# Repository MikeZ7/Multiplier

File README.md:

# Multiplier

Project of four quadrant multiplier for Systems and Electronics Circuits subject

---

## Project description
* Power Supply: (4V - 6V) DC
* Input signals range: (-1.5V - 1.5V) DC/AC
* PCB dimensions: 60x30mm 
* PCB components size: 0805
  
---

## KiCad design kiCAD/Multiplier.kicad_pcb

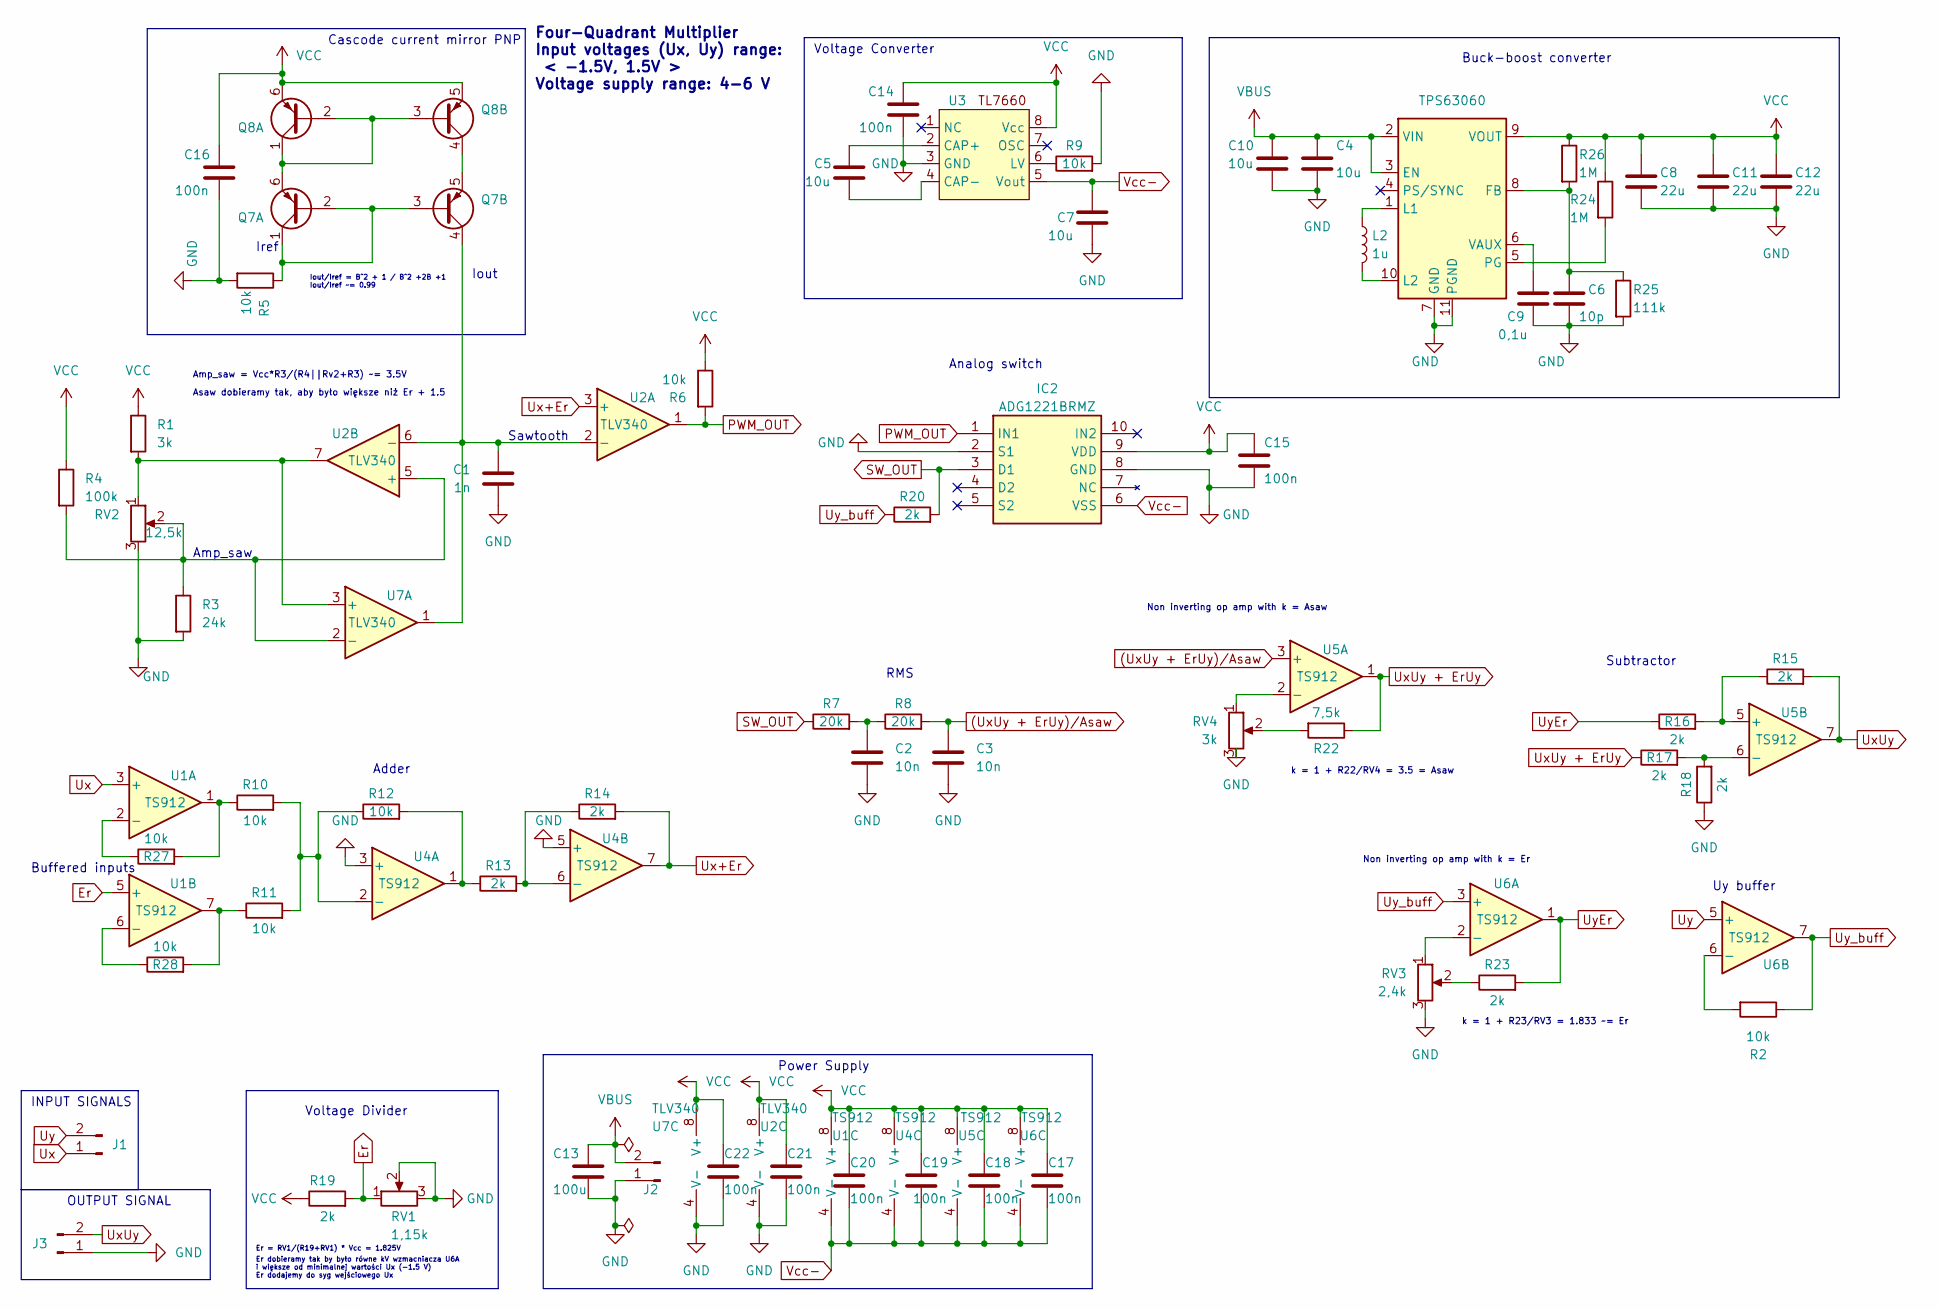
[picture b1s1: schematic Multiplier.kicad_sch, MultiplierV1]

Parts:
C1: 1n; C_0805_2012Metric
C2, C3: 10n; C_0805_2012Metric
C4, C5, C7, C10: 10u; C_0805_2012Metric
C6: 10p; C_0805_2012Metric
C8, C11, C12: 22u; C_0805_2012Metric
C9: 0,1u; C_0805_2012Metric
C13: 100u; CAP_293D-B_VSS
C14, C15, C16, C17, C18, C19, C20, C21, C22: 100n; C_0805_2012Metric
IC2: ADG1221BRMZ; RM_10_ADI; Mouser Part Number 584-ADG1221BRMZ
J1, J2, J3: Conn_01x02_Pin; PinHeader_1x02_P2.54mm_Vertical
L2: 1u; L_0805_2012Metric
Q7, Q8: Q_Dual_PNP_PNP_C1B1B2C2E2E1; SOT-363_DUAL_PNP
R1: 3k; R_0805_2012Metric_Pad1.20x1.40mm_HandSolder
R2, R5, R6, R9, R10, R11, R12, R27, R28: 10k; R_0805_2012Metric_Pad1.20x1.40mm_HandSolder
R3: 24k; R_0805_2012Metric_Pad1.20x1.40mm_HandSolder
R4: 100k; R_0805_2012Metric_Pad1.20x1.40mm_HandSolder
R7, R8: 20k; R_0805_2012Metric_Pad1.20x1.40mm_HandSolder
R13, R14, R15, R16, R17, R18, R19, R20, R23: 2k; R_0805_2012Metric_Pad1.20x1.40mm_HandSolder
R22: 7,5k; R_0805_2012Metric_Pad1.20x1.40mm_HandSolder
R24, R26: 1M; R_0805_2012Metric_Pad1.20x1.40mm_HandSolder
R25: 111k; R_0805_2012Metric_Pad1.20x1.40mm_HandSolder
RV1: 1,15k; Potentiometer_Bourns_3314G_Vertical
RV2: 12,5k; Potentiometer_Bourns_3314G_Vertical
RV3: 2,4k; Potentiometer_Bourns_3314G_Vertical
RV4: 3k; Potentiometer_Bourns_3314G_Vertical
U1, U4, U5, U6: TS912; TS912AIDT-SOIC8
U2, U7: TLV340; TLV3402IDR_SOIC8
U3: D8
U10: TPS63060; Texas_S-PWSON-N10_ThermalVias_Custom

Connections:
(UxUy + ErUy)/Asaw: C3.1, R8.2, U5.3 (+)
Er: R19.2, RV1.1, U1.5 (+)
GND: C1.2, C2.2, C3.2, C4.2, C6.2, C7.2, C8.2, C9.2, C10.2, C11.2, C12.2, C13.2, C14.2, C15.2, C16.2, C21.2, C22.2, IC2.2 (S1), IC2.8 (GND), J2.1, J3.1, R3.2, R5.2, R9.2, R18.1, R25.2, RV1.2, RV1.3, RV2.3, RV3.3, RV4.3, U2.4 (V-), U3.3 (GND), U4.3 (+), U4.5 (+), U7.4 (V-), U10.7 (GND), U10.11 (PGND); also elsewhere on the board
unnamed: C2.1, R7.2, R8.1
unnamed: Q7.1 (C1), Q7.2 (B1), Q7.3 (B2), R5.1
unnamed: Q7.6 (E1), Q8.1 (C1), Q8.2 (B1), Q8.3 (B2)
unnamed: C1.1, Q7.4 (C2), U2.2 (-), U2.6 (-), U7.1
unnamed: Q7.5 (E2), Q8.4 (C2)
unnamed: R10.1, R27.2, U1.1
unnamed: R11.1, R28.2, U1.7
unnamed: R12.2, R13.1, U4.1
unnamed: R22.2, RV4.2
unnamed: R23.1, RV3.2
unnamed: R27.1, U1.2 (-)
unnamed: R28.1, U1.6 (-)
unnamed: R3.1, R4.2, RV2.2, U2.5 (+), U7.2 (-)
unnamed: C5.1, U3.2 (CAP+)
unnamed: C5.2, U3.4 (CAP-)
unnamed: R9.1, U3.6 (LV)
unnamed: R10.2, R11.2, R12.1, U4.2 (-)
unnamed: R13.2, R14.1, U4.6 (-)
unnamed: RV4.1, U5.2 (-)
unnamed: R15.1, R16.2, U5.5 (+)
unnamed: R17.2, R18.2, U5.6 (-)
unnamed: RV3.1, U6.2 (-)
unnamed: R2.2, U6.6 (-)
unnamed: R1.2, RV2.1, U2.7, U7.3 (+)
unnamed: C6.1, R25.1, R26.2, U10.8 (FB)
unnamed: L2.1, U10.1 (L1)
unnamed: L2.2, U10.10 (L2)
unnamed: R24.2, U10.5 (PG)
unnamed: C9.1, U10.6 (VAUX)
PWM_OUT: IC2.1 (IN1), R6.2, U2.1
SW_OUT: IC2.3 (D1), R7.1, R20.2
Ux: J1.1, U1.3 (+); also elsewhere on the board
Ux+Er: R14.2, U2.3 (+), U4.7
UxUy: J3.2, R15.2, U5.7; also elsewhere on the board
UxUy + ErUy: R17.1, R22.1, U5.1
Uy: J1.2, U6.5 (+); also elsewhere on the board
UyEr: R16.1, R23.2, U6.1
Uy_buff: R2.1, R20.1, U6.3 (+), U6.7
VBUS: C4.1, C10.1, C13.1, J2.2, U10.2 (VIN), U10.3 (EN); also elsewhere on the board
VCC: C8.1, C11.1, C12.1, C14.1, C15.1, C16.1, C17.1, C18.1, C19.1, C20.1, C21.1, C22.1, IC2.9 (VDD), Q8.5 (E2), Q8.6 (E1), R1.1, R4.1, R6.1, R19.1, R24.1, R26.1, U1.8 (V+), U2.8 (V+), U3.8 (Vcc), U4.8 (V+), U5.8 (V+), U6.8 (V+), U7.8 (V+), U10.9 (VOUT)
Vcc-: C7.1, C17.2, C18.2, C19.2, C20.2, IC2.6 (VSS), U1.4 (V-), U3.5 (Vout), U4.4 (V-), U5.4 (V-), U6.4 (V-)

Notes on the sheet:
Non inverting op amp with k = Er
Cascode current mirror PNP
Iref
Analog switch
Iout
Iout/Iref = B^2 + 1 / B^2 +2B +1
OUTPUT SIGNAL
Non inverting op amp with k = Asaw
Buffered inputs
RMS
Amp_saw
Four-Quadrant Multiplier Input voltages (Ux, Uy) range: < -1.5V, 1.5V > Voltage supply range: 4-6 V
Er dobieramy tak by było równe kV wzmacniacza U6A i większe od minimalnej wartości Ux (-1.5 V) Er dodajemy do syg wejściowego Ux
Uy buffer
Adder
Asaw dobieramy tak, aby było większe niż Er + 1.5
INPUT SIGNALS
Er = RV1/(R19+RV1) * Vcc = 1.825V
Sawtooth
Subtractor
k = 1 + R22/RV4 = 3.5 = Asaw
Iout/Iref ~= 0.99
Power Supply
k = 1 + R23/RV3 = 1.833 ~= Er
Buck-boost converter
Voltage Divider
Amp_saw = Vcc*R3/(R4||Rv2+R3) ~= 3.5V
Voltage Converter

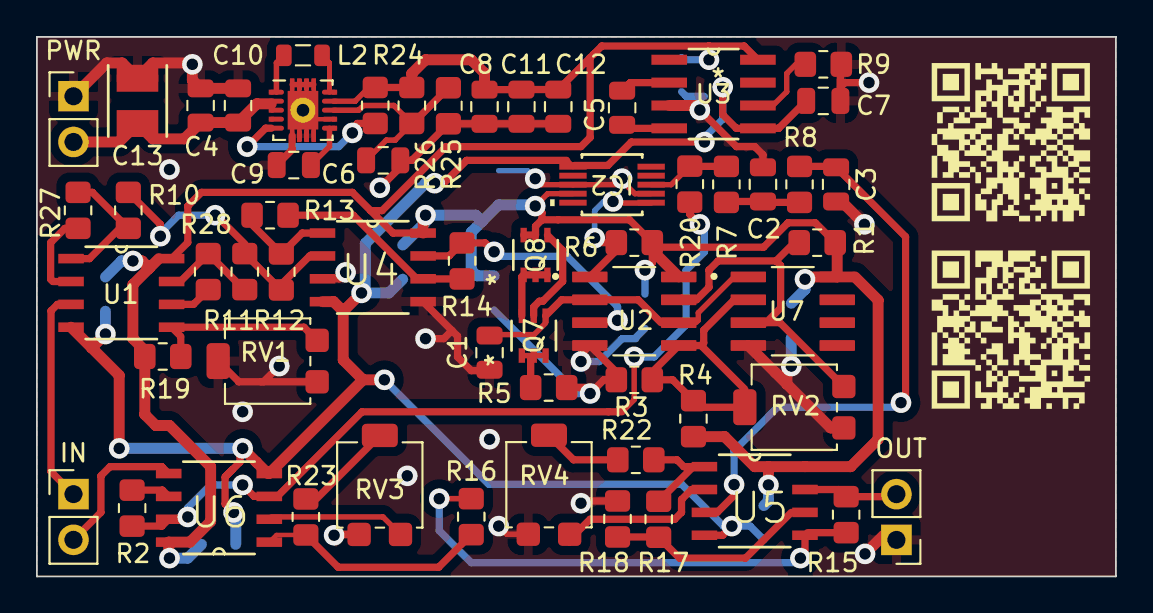
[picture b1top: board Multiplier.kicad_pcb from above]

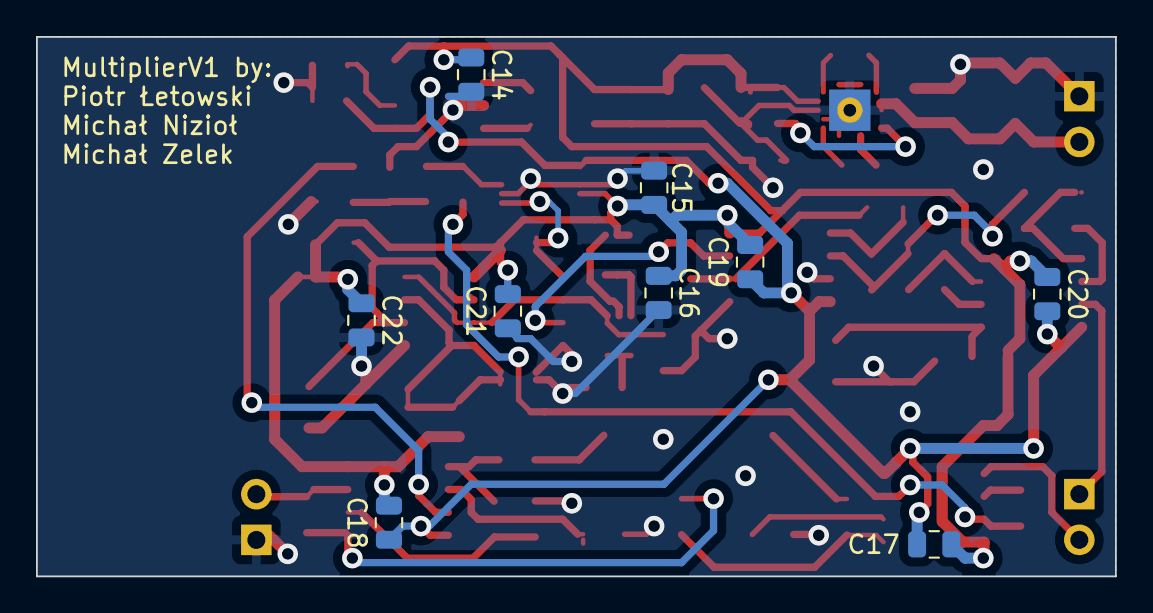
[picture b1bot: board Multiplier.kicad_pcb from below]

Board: 2 copper layers, 59.9 x 30.0 mm, 68 parts (9 on the bottom side), 44 nets.

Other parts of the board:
IN: Conn_01x02_Pin; PinHeader_1x02_P2.54mm_Vertical
OUT: Conn_01x02_Pin; PinHeader_1x02_P2.54mm_Vertical
PWR: Conn_01x02_Pin; PinHeader_1x02_P2.54mm_Vertical

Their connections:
GND: OUT.1, PWR.1; also elsewhere on the board
Ux: IN.1; also elsewhere on the board
UxUy: OUT.2; also elsewhere on the board
Uy: IN.2; also elsewhere on the board
VBUS: PWR.2; also elsewhere on the board

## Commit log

2023-11-21 Uploading the first version of Kicad project
2023-11-22 Adding image of multiplier schematics
2023-11-22 Update README.md
    Add schematics image
2023-11-22 Adding image of schematics
2023-11-22 Add Images and kiCAD directories to clean the mess
2023-11-24 Replacing schematics for TLV3402IDR assigning footpritns and adding first PCB layout
2023-11-24 adding potentiometer
2023-11-24 Modified: Multiplier.kicad_sch (resistors values)
2023-11-29 New footprint for buck-boost converter
2023-11-29 Initial routing and layout
2023-11-29 Modified: Multiplier.kicad_pcb, added: backups files
2023-11-30 Modified: Multiplier.kicad_pcb (fixed missing connections), added: backup files
2023-11-30 First PCB design with GND fields and tantalum (100nF) coupling capacitor added
2023-11-30 New footprint for TSP and tantalum capacitor
2023-11-30 Add tantalum cap footprint
2023-11-30 Finished first PCB prototype
2023-12-03 New schematic image, final PCB design
2023-12-03 Reloading branch
2023-12-03 Revert "Reloading branch"
    This reverts commit 17a884d624d71886552ad5c8232560fd1f52b29e.
2023-12-03 Final PCB version
2023-12-03 Final project
2023-12-03 Uploading images of PCB view
